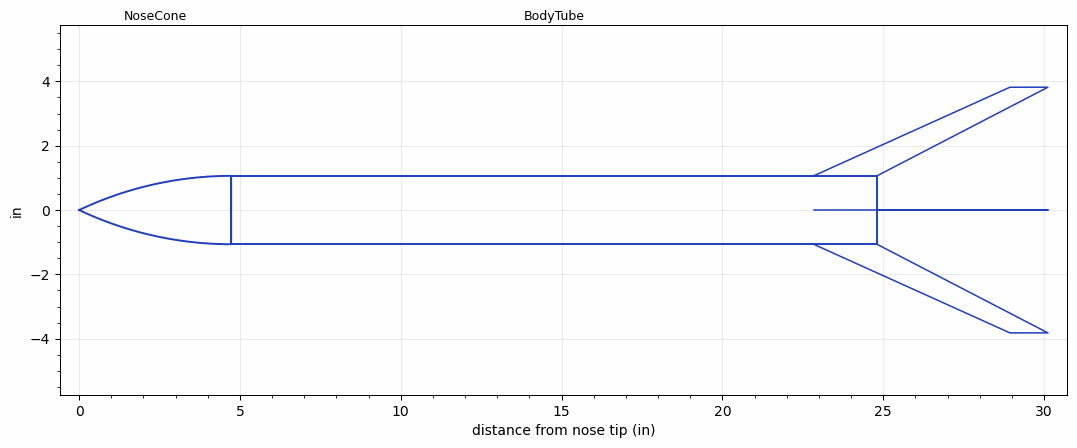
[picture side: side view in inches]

<RASAeroDocument>
 <FileVersion>2</FileVersion>
 <RocketDesign>
  <NoseCone>
   <Length>4.7244</Length>
   <Diameter>2.126</Diameter>
   <Shape>Tangent Ogive</Shape>
   <Location>0</Location>
  </NoseCone>
  <BodyTube>
   <Length>20.0787</Length>
   <Diameter>2.126</Diameter>
   <RailGuideDiameter>0.5512</RailGuideDiameter>
   <RailGuideHeight>0.378</RailGuideHeight>
   <Location>4.7244</Location>
   <Fin>
    <Count>4</Count>
    <Chord>1.9685</Chord>
    <Span>2.7559</Span>
    <SweepDistance>6.1023</SweepDistance>
    <TipChord>1.1811</TipChord>
    <Thickness>0.1181</Thickness>
    <Location>1.9685</Location>
    <AirfoilSection>Square</AirfoilSection>
   </Fin>
  </BodyTube>
  <Surface>Rough Camouflage Paint</Surface>
  <CD>0</CD>
  <ModifiedBarrowman>False</ModifiedBarrowman>
  <Turbulence>False</Turbulence>
  <UseBooster1>False</UseBooster1>
  <UseBooster2>False</UseBooster2>
 </RocketDesign>
 <LaunchSite>
  <Altitude>0</Altitude>
  <Pressure>29.9214</Pressure>
  <RodAngle>0</RodAngle>
  <RodLength>39.37</RodLength>
  <Temperature>59</Temperature>
  <WindSpeed>4.4739</WindSpeed>
 </LaunchSite>
 <Recovery>
  <Altitude1>0</Altitude1>
  <Altitude2>0</Altitude2>
  <DeviceType1>None</DeviceType1>
  <DeviceType2>None</DeviceType2>
  <Event1>False</Event1>
  <Event2>False</Event2>
  <Size1>0</Size1>
  <Size2>0</Size2>
  <EventType1>None</EventType1>
  <EventType2>None</EventType2>
  <CD1>0</CD1>
  <CD2>0</CD2>
 </Recovery>
 <SimulationList>
  <Simulation>
   <SustainerLaunchWt>0.8859</SustainerLaunchWt>
   <SustainerCG>17.7695</SustainerCG>
   <SustainerIgnitionDelay>0</SustainerIgnitionDelay>
   <Booster1SeparationDelay>0</Booster1SeparationDelay>
   <Booster1IgnitionDelay>0</Booster1IgnitionDelay>
   <IncludeBooster1>False</IncludeBooster1>
   <Booster2Delay>0</Booster2Delay>
   <IncludeBooster2>False</IncludeBooster2>
  </Simulation>
 </SimulationList>
</RASAeroDocument>
